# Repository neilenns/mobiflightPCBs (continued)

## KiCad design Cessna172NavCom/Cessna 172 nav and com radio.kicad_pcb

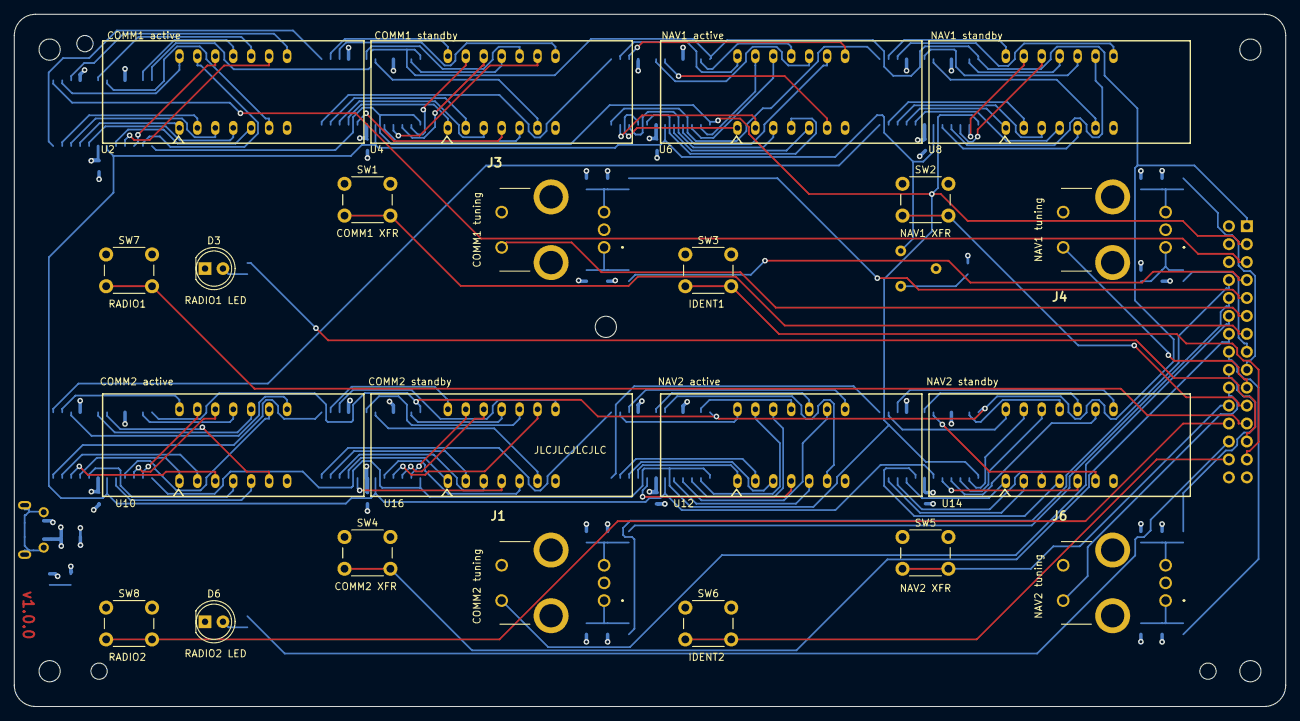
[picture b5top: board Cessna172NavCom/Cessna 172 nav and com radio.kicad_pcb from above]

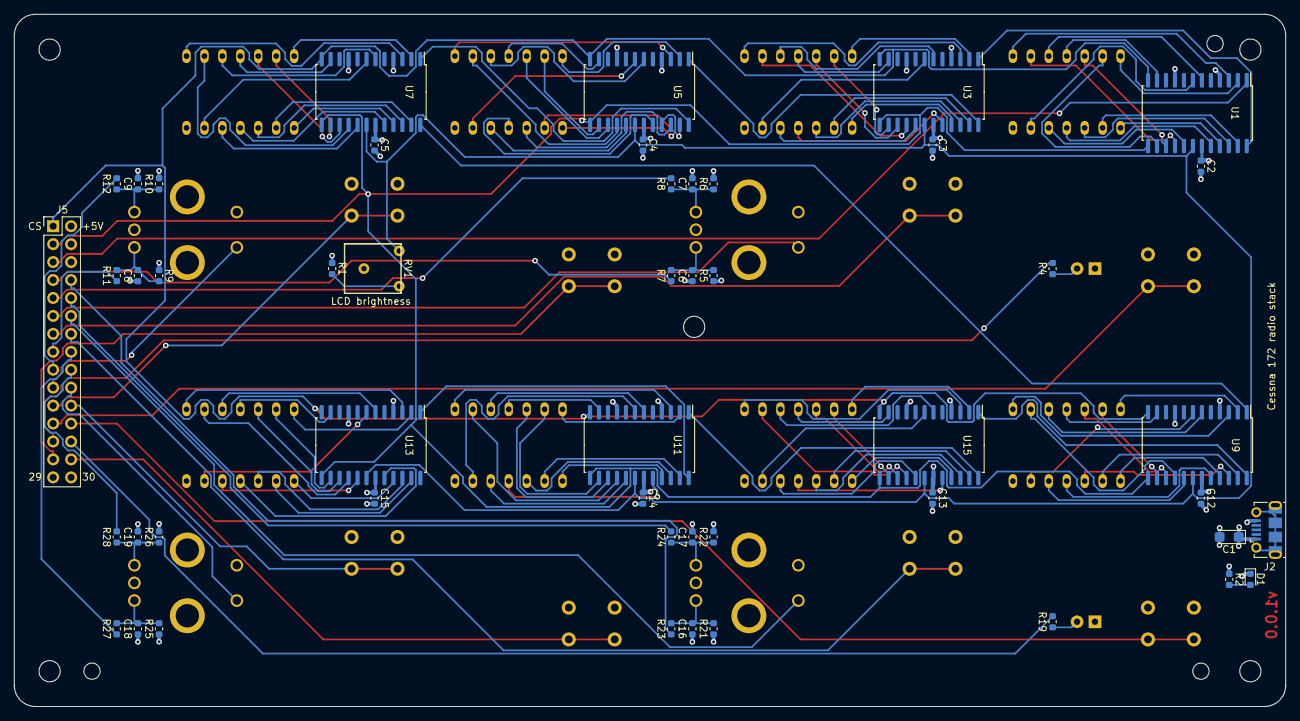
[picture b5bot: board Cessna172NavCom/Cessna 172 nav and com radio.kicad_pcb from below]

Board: 4 copper layers, 180.0 x 98.0 mm, 76 parts (49 on the bottom side), 151 nets.

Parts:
C1: 10uF; CP_EIA-3216-18_Kemet-A
C2, C3, C4, C5, C12, C13, C14, C15: 0.1uF; C_0603_1608Metric
C6, C7, C8, C9, C16, C17, C18, C19: 0.01uf; C_0603_1608Metric
D1: LED; LED_0603_1608Metric
D3, D6: LED; LED_D5.0mm
H1, H2, H3, H4, H5: MountingHole_3mm
J1, J3, J4, J6: EN11-HSM1BF20; EN11HSM1BF20
J2: USB_B_Micro; USB_Micro-B_Molex-105017-0001
J5: Conn_02x15_Odd_Even; PinHeader_2x15_P2.54mm_Vertical
R1, R2, R4, R19: 220k; R_0603_1608Metric
R5, R6, R7, R8, R9, R10, R11, R12, R21, R22, R23, R24, R25, R26, R27, R28: 10k; R_0603_1608Metric
RV1: 100k; A-2506 trimpot resistor
SW1, SW2, SW3, SW4, SW5, SW6, SW7, SW8: SW_Push; SW_PUSH_6mm_H8mm
U1, U3, U5, U7, U9, U11, U13, U15: MAX7219 COM standby; SOIC-24W_7.5x15.4mm_P1.27mm
U2, U4, U6, U8, U10, U12, U14, U16: 3651A

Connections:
+5V: C1.1, C2.1, C3.1, C4.1, C5.1, C12.1, C13.1, C14.1, C15.1, J2.1, J5.2, R1.1, R2.1, R5.1, R6.2, R9.1, R10.2, R21.1, R22.2, R25.1, R26.2, U1.19, U3.19, U5.19, U7.19, U9.19, U11.19, U13.19, U15.19
/5 digit LCD display/DIG_0: U1.2, U2.14
/5 digit LCD display/DIG_1: U1.11, U2.11
/5 digit LCD display/DIG_2: U1.6, U2.10
/5 digit LCD display/DIG_3: U1.7, U2.6
/5 digit LCD display/DIG_4: U1.3, U2.8
/5 digit LCD display/SEG_A: U1.14, U2.13
/5 digit LCD display/SEG_B: U1.16, U2.9
/5 digit LCD display/SEG_C: U1.20, U2.4
/5 digit LCD display/SEG_D: U1.23, U2.2
/5 digit LCD display/SEG_DP: U1.22, U2.3
/5 digit LCD display/SEG_E: U1.21, U2.1
/5 digit LCD display/SEG_F: U1.15, U2.12
/5 digit LCD display/SEG_G: U1.17, U2.5
/Tuning rotary encoder and switch/A1: C6.2, J3.A1, R5.2, R7.2
/Tuning rotary encoder and switch/B1: C7.1, J3.B1, R6.1, R8.1
/sheet5F5DD32A/A1: C8.2, J4.A1, R9.2, R11.2
/sheet5F5DD32A/B1: C9.1, J4.B1, R10.1, R12.1
/sheet5F68A9C2/DIG_0: U9.2, U10.14
/sheet5F68A9C2/DIG_1: U9.11, U10.11
/sheet5F68A9C2/DIG_2: U9.6, U10.10
/sheet5F68A9C2/DIG_3: U9.7, U10.6
/sheet5F68A9C2/DIG_4: U9.3, U10.8
/sheet5F68A9C2/DIN: U7.24, U9.1
/sheet5F68A9C2/SEG_A: U9.14, U10.13
/sheet5F68A9C2/SEG_B: U9.16, U10.9
/sheet5F68A9C2/SEG_C: U9.20, U10.4
/sheet5F68A9C2/SEG_D: U9.23, U10.2
/sheet5F68A9C2/SEG_DP: U9.22, U10.3
/sheet5F68A9C2/SEG_E: U9.21, U10.1
/sheet5F68A9C2/SEG_F: U9.15, U10.12
/sheet5F68A9C2/SEG_G: U9.17, U10.5
/sheet5F68A9C3/DIG_0: U11.2, U12.14
/sheet5F68A9C3/DIG_1: U11.11, U12.11
/sheet5F68A9C3/DIG_2: U11.6, U12.10
/sheet5F68A9C3/DIG_3: U11.7, U12.6
/sheet5F68A9C3/DIG_4: U11.3, U12.8
/sheet5F68A9C3/DIN: U11.1, U15.24
/sheet5F68A9C3/SEG_A: U11.14, U12.13
/sheet5F68A9C3/SEG_B: U11.16, U12.9
/sheet5F68A9C3/SEG_C: U11.20, U12.4
/sheet5F68A9C3/SEG_D: U11.23, U12.2
/sheet5F68A9C3/SEG_DP: U11.22, U12.3
/sheet5F68A9C3/SEG_E: U11.21, U12.1
/sheet5F68A9C3/SEG_F: U11.15, U12.12
/sheet5F68A9C3/SEG_G: U11.17, U12.5
/sheet5F68A9C4/DIG_0: U13.2, U14.14
/sheet5F68A9C4/DIG_1: U13.11, U14.11
/sheet5F68A9C4/DIG_2: U13.6, U14.10
/sheet5F68A9C4/DIG_3: U13.7, U14.6
/sheet5F68A9C4/DIG_4: U13.3, U14.8
/sheet5F68A9C4/DIN: U11.24, U13.1
/sheet5F68A9C4/SEG_A: U13.14, U14.13
/sheet5F68A9C4/SEG_B: U13.16, U14.9
/sheet5F68A9C4/SEG_C: U13.20, U14.4
/sheet5F68A9C4/SEG_D: U13.23, U14.2
/sheet5F68A9C4/SEG_DP: U13.22, U14.3
/sheet5F68A9C4/SEG_E: U13.21, U14.1
/sheet5F68A9C4/SEG_F: U13.15, U14.12
/sheet5F68A9C4/SEG_G: U13.17, U14.5
/sheet5F68A9C5/DIG_0: U15.2, U16.14
/sheet5F68A9C5/DIG_1: U15.11, U16.11
/sheet5F68A9C5/DIG_2: U15.6, U16.10
/sheet5F68A9C5/DIG_3: U15.7, U16.6
/sheet5F68A9C5/DIG_4: U15.3, U16.8
/sheet5F68A9C5/DIN: U9.24, U15.1
/sheet5F68A9C5/SEG_A: U15.14, U16.13
/sheet5F68A9C5/SEG_B: U15.16, U16.9
/sheet5F68A9C5/SEG_C: U15.20, U16.4
/sheet5F68A9C5/SEG_D: U15.23, U16.2
/sheet5F68A9C5/SEG_DP: U15.22, U16.3
/sheet5F68A9C5/SEG_E: U15.21, U16.1
/sheet5F68A9C5/SEG_F: U15.15, U16.12
/sheet5F68A9C5/SEG_G: U15.17, U16.5
/sheet5F71BCD2/A1: C16.2, J1.A1, R21.2, R23.2
/sheet5F71BCD2/B1: C17.1, J1.B1, R22.1, R24.1
/sheet5F71BCD3/A1: C18.2, J6.A1, R25.2, R27.2
/sheet5F71BCD3/B1: C19.1, J6.B1, R26.1, R28.1
/sheet5F611637/DIG_0: U3.2, U4.14
/sheet5F611637/DIG_1: U3.11, U4.11
/sheet5F611637/DIG_2: U3.6, U4.10
/sheet5F611637/DIG_3: U3.7, U4.6
/sheet5F611637/DIG_4: U3.3, U4.8
/sheet5F611637/DIN: U1.24, U3.1
/sheet5F611637/SEG_A: U3.14, U4.13
/sheet5F611637/SEG_B: U3.16, U4.9
/sheet5F611637/SEG_C: U3.20, U4.4
/sheet5F611637/SEG_D: U3.23, U4.2
/sheet5F611637/SEG_DP: U3.22, U4.3
/sheet5F611637/SEG_E: U3.21, U4.1
/sheet5F611637/SEG_F: U3.15, U4.12
/sheet5F611637/SEG_G: U3.17, U4.5
/sheet5F613960/DIG_0: U5.2, U6.14
/sheet5F613960/DIG_1: U5.11, U6.11
/sheet5F613960/DIG_2: U5.6, U6.10
/sheet5F613960/DIG_3: U5.7, U6.6
/sheet5F613960/DIG_4: U5.3, U6.8
/sheet5F613960/DIN: U3.24, U5.1
/sheet5F613960/SEG_A: U5.14, U6.13
/sheet5F613960/SEG_B: U5.16, U6.9
/sheet5F613960/SEG_C: U5.20, U6.4
/sheet5F613960/SEG_D: U5.23, U6.2
/sheet5F613960/SEG_DP: U5.22, U6.3
/sheet5F613960/SEG_E: U5.21, U6.1
/sheet5F613960/SEG_F: U5.15, U6.12
/sheet5F613960/SEG_G: U5.17, U6.5
/sheet5F613961/DIG_0: U7.2, U8.14
/sheet5F613961/DIG_1: U7.11, U8.11
/sheet5F613961/DIG_2: U7.6, U8.10
/sheet5F613961/DIG_3: U7.7, U8.6
/sheet5F613961/DIG_4: U7.3, U8.8
/sheet5F613961/DIN: U5.24, U7.1
/sheet5F613961/SEG_A: U7.14, U8.13
/sheet5F613961/SEG_B: U7.16, U8.9
/sheet5F613961/SEG_C: U7.20, U8.4
/sheet5F613961/SEG_D: U7.23, U8.2
/sheet5F613961/SEG_DP: U7.22, U8.3
/sheet5F613961/SEG_E: U7.21, U8.1
/sheet5F613961/SEG_F: U7.15, U8.12
/sheet5F613961/SEG_G: U7.17, U8.5
CLK: J5.3, U1.13, U3.13, U5.13, U7.13, U9.13, U11.13, U13.13, U15.13
COMM1_KHZ_SW: J3.D1, J5.11
COMM1_LEFT: J5.7, R7.1
COMM1_RIGHT: J5.9, R8.2
COMM1_XFR: J5.13, SW1.2
COMM2_KHZ_SW: J1.D1, J5.12
COMM2_LEFT: J5.8, R23.1
COMM2_RIGHT: J5.10, R24.2
COMM2_XFR: J5.14, SW4.2
CS_LOAD: J5.1, U1.12, U3.12, U5.12, U7.12, U9.12, U11.12, U13.12, U15.12
DIN: J5.5, U1.1
GND: C1.2, C2.2, C3.2, C4.2, C5.2, C6.1, C7.2, C8.1, C9.2, C12.2, C13.2, C14.2, C15.2, C16.1, C17.2, C18.1, C19.2, D1.1, D3.1, D6.1, J1.C1, J1.E1, J2.5, J3.C1, J3.E1, J4.C1, J4.E1, J5.4, J5.29, J5.30, J6.C1, J6.E1, SW1.1, SW2.1, SW3.1, SW4.1, SW5.1, SW6.1, SW7.1, SW8.1, U1.4, U1.9, U3.4, U3.9, U5.4, U5.9, U7.4, U7.9, U9.4, U9.9, U11.4, U11.9, U13.4, U13.9, U15.4, U15.9
IDENT1_SW: J5.27, SW3.2
IDENT2_SW: J5.28, SW6.2
ISET: RV1.3, U1.18, U3.18, U5.18, U7.18, U9.18, U11.18, U13.18, U15.18
NAV1_KHZ_SW: J4.D1, J5.19
NAV1_LEFT: J5.15, R11.1
NAV1_RIGHT: J5.17, R12.2
NAV1_XFR: J5.21, SW2.2
NAV2_KHZ_SW: J5.20, J6.D1
NAV2_LEFT: J5.16, R27.1
NAV2_RIGHT: J5.18, R28.2
NAV2_XFR: J5.22, SW5.2
unnamed: D1.2, R2.2
unnamed: D3.2, R4.1
unnamed: D6.2, R19.1
unnamed: R1.2, RV1.1
RADIO1_LED: J5.25, R4.2
RADIO1_SW: J5.23, SW7.2
RADIO2_LED: J5.26, R19.2
RADIO2_SW: J5.24, SW8.2

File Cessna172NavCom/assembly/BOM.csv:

Comment,Designator,Footprint,LCSC
"10uF","C1","Capacitor_THT:CP_Radial_D5.0mm_P2.00mm",""
"0.1uF","C2,C3,C4,C5,C12,C13,C14,C15","Capacitor_SMD:C_0805_2012Metric_Pad1.15x1.40mm_HandSolder"," C49678"
"0.01uf","C6,C7,C8,C9,C16,C17,C18,C19","Capacitor_SMD:C_0805_2012Metric_Pad1.15x1.40mm_HandSolder"," C1710"
"LED","D1","LED_SMD:LED_0805_2012Metric_Pad1.15x1.40mm_HandSolder","C2293"
"LED","D3,D6","LED_THT:LED_D5.0mm",""
"USB_B_Micro","J2","Connector_USB:USB_Micro-B_Molex-105017-0001",""
"EN11-HSM1BF20","J1,J3,J4,J6","SamacSys_Parts:EN11HSM1BF20",""
"Conn_02x15_Odd_Even","J5","Connector_PinHeader_2.54mm:PinHeader_2x15_P2.54mm_Vertical",""
"220","R1,R2,R4,R19","Resistor_SMD:R_0805_2012Metric_Pad1.15x1.40mm_HandSolder","C17540"
"10k","R5,R6,R7,R8,R9,R10,R11,R12,R21,R22,R23,R24,R25,R26,R27,R28","Resistor_SMD:R_0805_2012Metric_Pad1.15x1.40mm_HandSolder","C17414"
"100k","RV1","Cessna 172 nav and com radio:A-2506 trimpot resistor",""
"SW_Push","SW1,SW2,SW3,SW4,SW5,SW6,SW7,SW8","Button_Switch_THT:SW_PUSH_6mm_H8mm",""
"MAX7219 COM standby","U1,U3,U5,U7,U9,U11,U13,U15","Package_SO:SOIC-24W_7.5x15.4mm_P1.27mm","C9964"
"3651A","U2,U4,U6,U8,U10,U12,U14,U16","Cessna 172 nav and com radio:3651A",""

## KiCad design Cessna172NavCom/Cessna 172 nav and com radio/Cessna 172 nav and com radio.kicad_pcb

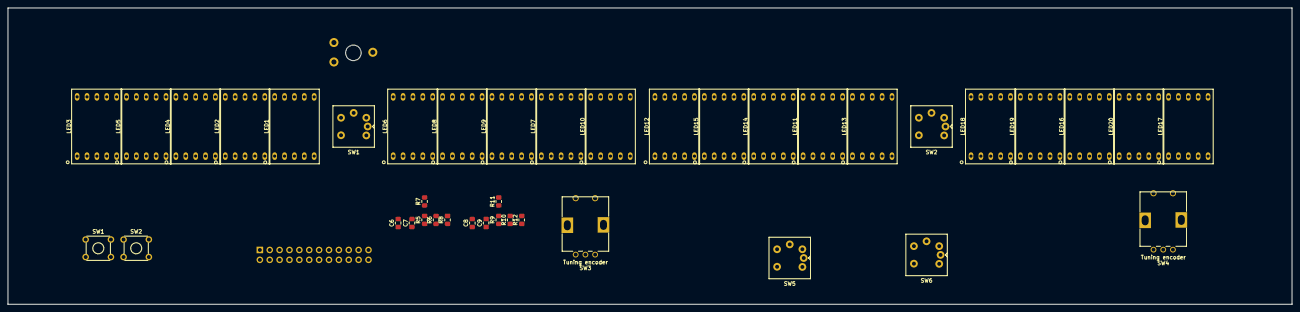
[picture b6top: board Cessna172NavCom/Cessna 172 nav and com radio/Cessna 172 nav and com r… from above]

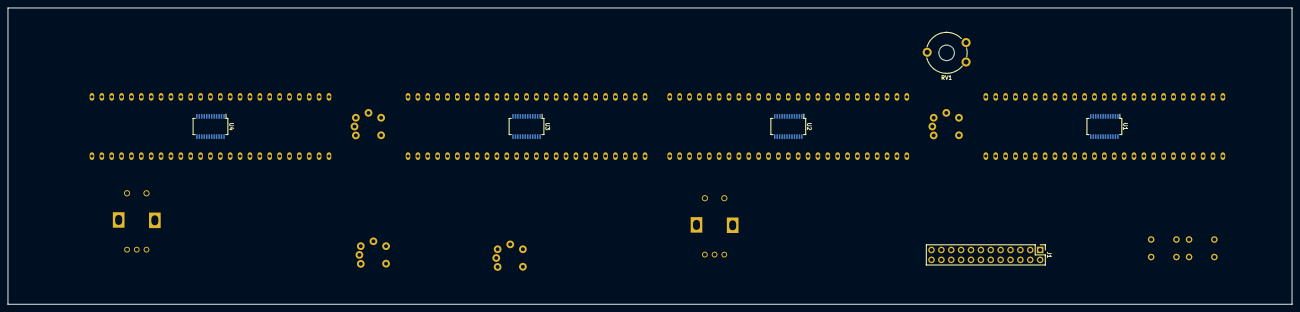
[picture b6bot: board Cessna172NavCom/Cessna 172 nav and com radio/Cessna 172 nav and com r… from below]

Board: 2 copper layers, 330.2 x 76.2 mm, 46 parts (6 on the bottom side), 77 nets, no tracks yet.

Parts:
C6, C7, C8, C9: 0.1uf; C_0805_2012Metric_Pad1.15x1.40mm_HandSolder
J1: Conn_02x12_Odd_Even; PinHeader_2x12_P2.54mm_Vertical
LED1, LED6, LED11, LED16: MobiFlight digit 5; KYX-5101AS
LED2, LED7, LED12, LED17: MobiFlight digit 4; KYX-5101AS
LED3, LED8, LED13, LED18: MobiFlight digit 2; KYX-5101AS
LED4, LED9, LED14, LED19: MobiFlight digit 1; KYX-5101AS
LED5, LED10, LED15, LED20: Mobiflight digit 0; KYX-5101AS
R5, R6, R7, R8, R9, R10, R11, R12: 10k; R_0805_2012Metric_Pad1.15x1.40mm_HandSolder
RV1: 100k; Potentiometer_Piher_PT-10-V10_Vertical_Hole
SW1: COMM transfer switch; SW_TH_Tactile_Omron_B3F-10xx
SW1#2: COMM toggle; B3W-9000-xxx
SW2: NAV transfer switch; SW_TH_Tactile_Omron_B3F-10xx
SW2#2: NAV toggle; B3W-9000-xxx
SW3, SW4: Tuning encoder; EN11-HSM1BF20
SW5: Test switch; B3W-9000-xxx
SW6: Ident switch; B3W-9000-xxx
U1, U2, U3, U4: MAX7219 COM standby; SSOP-24_3.9x8.7mm_P0.635mm

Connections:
+5V: J1.1, R5.2, R6.2, R9.2, R10.2, U1.19, U2.19, U3.19, U4.19
/5 digit LCD display/DIG_0: LED5.8, U1.2
/5 digit LCD display/DIG_1: LED4.8, U1.11
/5 digit LCD display/DIG_2: LED3.8, U1.6
/5 digit LCD display/DIG_3: LED2.8, U1.7
/5 digit LCD display/DIG_4: LED1.8, U1.3
/5 digit LCD display/SEG_A: LED1.7, LED2.7, LED3.7, LED4.7, LED5.7, U1.14
/5 digit LCD display/SEG_B: LED1.6, LED2.6, LED3.6, LED4.6, LED5.6, U1.16
/5 digit LCD display/SEG_C: LED1.4, LED2.4, LED3.4, LED4.4, LED5.4, U1.20
/5 digit LCD display/SEG_D: LED1.2, LED2.2, LED3.2, LED4.2, LED5.2, U1.23
/5 digit LCD display/SEG_DP: LED1.5, LED2.5, LED3.5, LED4.5, LED5.5, U1.22
/5 digit LCD display/SEG_E: LED1.1, LED2.1, LED3.1, LED4.1, LED5.1, U1.21
/5 digit LCD display/SEG_F: LED1.9, LED2.9, LED3.9, LED4.9, LED5.9, U1.15
/5 digit LCD display/SEG_G: LED1.10, LED2.10, LED3.10, LED4.10, LED5.10, U1.17
/sheet5F611637/DIG_0: LED10.8, U2.2
/sheet5F611637/DIG_1: LED9.8, U2.11
/sheet5F611637/DIG_2: LED8.8, U2.6
/sheet5F611637/DIG_3: LED7.8, U2.7
/sheet5F611637/DIG_4: LED6.8, U2.3
/sheet5F611637/DIN: U1.24, U2.1
/sheet5F611637/SEG_A: LED6.7, LED7.7, LED8.7, LED9.7, LED10.7, U2.14
/sheet5F611637/SEG_B: LED6.6, LED7.6, LED8.6, LED9.6, LED10.6, U2.16
/sheet5F611637/SEG_C: LED6.4, LED7.4, LED8.4, LED9.4, LED10.4, U2.20
/sheet5F611637/SEG_D: LED6.2, LED7.2, LED8.2, LED9.2, LED10.2, U2.23
/sheet5F611637/SEG_DP: LED6.5, LED7.5, LED8.5, LED9.5, LED10.5, U2.22
/sheet5F611637/SEG_E: LED6.1, LED7.1, LED8.1, LED9.1, LED10.1, U2.21
/sheet5F611637/SEG_F: LED6.9, LED7.9, LED8.9, LED9.9, LED10.9, U2.15
/sheet5F611637/SEG_G: LED6.10, LED7.10, LED8.10, LED9.10, LED10.10, U2.17
/sheet5F613960/DIG_0: LED15.8, U3.2
/sheet5F613960/DIG_1: LED14.8, U3.11
/sheet5F613960/DIG_2: LED13.8, U3.6
/sheet5F613960/DIG_3: LED12.8, U3.7
/sheet5F613960/DIG_4: LED11.8, U3.3
/sheet5F613960/DIN: U2.24, U3.1
/sheet5F613960/SEG_A: LED11.7, LED12.7, LED13.7, LED14.7, LED15.7, U3.14
/sheet5F613960/SEG_B: LED11.6, LED12.6, LED13.6, LED14.6, LED15.6, U3.16
/sheet5F613960/SEG_C: LED11.4, LED12.4, LED13.4, LED14.4, LED15.4, U3.20
/sheet5F613960/SEG_D: LED11.2, LED12.2, LED13.2, LED14.2, LED15.2, U3.23
/sheet5F613960/SEG_DP: LED11.5, LED12.5, LED13.5, LED14.5, LED15.5, U3.22
/sheet5F613960/SEG_E: LED11.1, LED12.1, LED13.1, LED14.1, LED15.1, U3.21
/sheet5F613960/SEG_F: LED11.9, LED12.9, LED13.9, LED14.9, LED15.9, U3.15
/sheet5F613960/SEG_G: LED11.10, LED12.10, LED13.10, LED14.10, LED15.10, U3.17
/sheet5F613961/DIG_0: LED20.8, U4.2
/sheet5F613961/DIG_1: LED19.8, U4.11
/sheet5F613961/DIG_2: LED18.8, U4.6
/sheet5F613961/DIG_3: LED17.8, U4.7
/sheet5F613961/DIG_4: LED16.8, U4.3
/sheet5F613961/DIN: U3.24, U4.1
/sheet5F613961/SEG_A: LED16.7, LED17.7, LED18.7, LED19.7, LED20.7, U4.14
/sheet5F613961/SEG_B: LED16.6, LED17.6, LED18.6, LED19.6, LED20.6, U4.16
/sheet5F613961/SEG_C: LED16.4, LED17.4, LED18.4, LED19.4, LED20.4, U4.20
/sheet5F613961/SEG_D: LED16.2, LED17.2, LED18.2, LED19.2, LED20.2, U4.23
/sheet5F613961/SEG_DP: LED16.5, LED17.5, LED18.5, LED19.5, LED20.5, U4.22
/sheet5F613961/SEG_E: LED16.1, LED17.1, LED18.1, LED19.1, LED20.1, U4.21
/sheet5F613961/SEG_F: LED16.9, LED17.9, LED18.9, LED19.9, LED20.9, U4.15
/sheet5F613961/SEG_G: LED16.10, LED17.10, LED18.10, LED19.10, LED20.10, U4.17
CLK: J1.4, U1.13, U2.13, U3.13, U4.13
COMM_LEFT: J1.8, R8.2
COMM_RIGHT: J1.10, R7.1
COMM_TX_LED: J1.16, SW1.4, SW1#2.6
COMM_TX_SW: J1.14, SW1.2, SW1#2.4
DIN: J1.6, U1.1
GND: C6.1, C7.2, C8.1, C9.2, J1.3, SW1.1, SW1.3, SW1#2.3, SW1#2.5, SW2.1, SW2.3, SW2#2.3, SW2#2.5, SW5.3, SW5.5, SW6.3, SW6.5, U1.4, U1.9, U2.4, U2.9, U3.4, U3.9, U4.4, U4.9
IDENT_LED: J1.23, SW6.6
IDENT_SW: J1.21, SW6.4
ISET: RV1.3, U1.18, U2.18, U3.18, U4.18
LOAD: J1.2, U1.12, U2.12, U3.12, U4.12
NAV_LEFT: J1.5, R12.2
NAV_RIGHT: J1.7, R11.1
NAV_TX_LED: J1.13, SW2.4, SW2#2.6
NAV_TX_SW: J1.11, SW2.2, SW2#2.4
unnamed: C6.2, R5.1, R7.2
unnamed: C7.1, R6.1, R8.1
unnamed: C8.2, R9.1, R11.2
unnamed: C9.1, R10.1, R12.1
TEST_LED: J1.20, SW5.6
TEST_SW: J1.18, SW5.4

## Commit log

2020-09-12 Initial schema
2020-09-12 Minor update
2020-09-12 Five digit displays wired up
2020-09-12 Add rotary encoder
2020-09-12 3D model for LED
2020-09-12 3d model updates
2020-09-12 Updated schematic to include remaining items.
2020-09-12 Proper LED buttons and switches
2020-09-12 More 3D models, footprints, and manuals
2020-09-12 Switch footprint
2020-09-12 Tactile switch
2020-09-13 Fix up paths
2020-09-13 Traces for one LCD bank complete
2020-09-13 LEDs and power jack
2020-09-13 First full layout attempt, new 3D models
2020-09-13 Re-work to use 5 digit LEDs
2020-09-15 New board size!
2020-09-17 Switch to USB for power, all parts on board
2020-09-17 Updated board size and parts placement
2020-09-17 Updated rotary encoder with proper footprint
2020-09-17 Connection, footprint, and layout updates
2020-09-18 Auto-router files
2020-09-18 Updated trace width for +5V and GND
2020-09-18 Mostly laid out
2020-09-18 Full 2up layout done
2020-09-19 Position changes for routing
2020-09-19 Move things around to try and help router
2020-09-19 Fix courtyard overlap for routing
2020-09-19 New encoder design
2020-09-19 Fully routed woot woot!
2020-09-19 Fully routed!!!
2020-09-19 Minor PCB cleanup
2020-09-22 Add mobiflight files, start Arduino shield
2020-09-22 Remaining encoders and some buttons confirmed
2020-09-23 All comm and nav radio freq set and swap tested
2020-09-23 Remove unnecessary items, rename some of the nets
2020-09-23 Switch to 30 pin connector for availability reasons
2020-09-23 Schematic renumbering
2020-09-24 Arduino shield plus more main board changes
2020-09-24 Added autoroute and pour
2020-09-24 Re-routed with new LED position
2020-09-26 Finally done maybe for real
2020-09-26 Smaller components and output for JLC
2020-09-26 Ready for 0805 production
2020-09-27 Final version submitted for assembly
2020-10-08 Configs that work with the v1 board
2020-10-08 A bunch of the knobs are working now
2020-10-09 Working on a new board
2020-10-09 New board ready
2020-10-10 Updated secondary display
2020-10-11 more autopilot changes
2020-10-12 Submitted version!
2020-11-05 Mobiflight config for actual build
2021-07-20 Updated mobiflight configurations to use SimConnect events
2021-07-29 Add new board for TBM930
2021-07-30 TBM930 updates
2021-08-14 Switch to use the LED driver chip
2021-08-15 Create global library for footprints and symbols
2021-08-16 Massive de-ice panel update
2021-08-16 Routed!
2021-08-16 Before switching to Pro Micro
2021-08-16 Switch to smaller Arduino
2021-08-16 More PCB markings
2021-08-17 Minor changes
2021-08-18 Microcontroller righton the board
2021-08-18 Placed components on PCB, working on routing
2021-08-19 More atmega32u4 routing
2021-08-19 Everything is routed!
2021-08-19 Schematic submitted to microtype
2021-08-19 Schematic updates based on MT engineering discord feedback
2021-08-20 Additional reset components
2021-08-20 Fix 12V routing
2021-08-21 Massive PCB reroute
2021-08-21 Fully routed v2
2021-08-23 Switch to TQFP
2021-08-23 Lots of minor updates to silk screen and vias
2021-08-24 USB breakout board
2021-08-24 Add labels, change header
2021-08-25 Adjust the spacing of PCB components, reroute data trace
2021-08-25 Swap to different USB footprint
2021-08-25 More footprint changes
2021-08-25 Upsize all the connectors
2021-08-26 Final gerbers for USB breakout board
2021-08-26 Change connector, fix BOM
2021-09-04 Breakout board and tbm930 board updates
2021-09-05 Remove old files
2021-09-06 Update to support the new board!
2021-09-07 Cleanup references so it should open on any machine
2021-09-07 Move MobiFlight config into de-ice panel folder
2021-09-07 Add missing BOM and TBM930 mods
2021-09-07 Add missing BOM files
2021-09-09 Fix errors in the panel configs
2021-09-11 Initial version
2021-09-11 Add all the inputs
2021-09-15 More AP updates
2021-09-15 Add bom for de-ice panel
2021-09-15 Move ibom to gh pages
2021-09-16 Add schematic PDF
2021-09-16 Testing kibot in github actions
2021-09-16 Try single quotes
2021-09-16 Add manual trigger
2021-09-16 Remove manual trigger
2021-09-16 Try without spaces in folder name
2021-09-16 Remove spaces from filenames
2021-09-16 Change case
2021-09-16 Update outputs generated
2021-09-16 Remove logo file
2021-09-16 Remove more logos
2021-09-16 Add JLCPCB pos and BOM files
2021-09-16 Add JLCPCB BOM and pos files
2021-09-16 Fix YAML errors
2021-09-16 Try fixing rotation
2021-09-16 Try fixing exclude filter
2021-09-16 Fix JLCPCB generation
2021-09-16 Add VSCode dev container for KiBot
2021-09-16 Move all fab files to dedicated folder
2021-09-16 Working ibom generation, JLCPCB generation
2021-09-16 Fix PCB holes
2021-09-16 Fix silkscreen position
2021-09-16 Everything working!
2021-09-16 Add version numbers and license
2021-09-16 Enable ERC/DRC/fills
2021-09-16 Refactor yaml and fix github action
2021-09-16 Change footprint for terminal block
2021-09-16 Commit to trigger workflow
2021-09-16 Fix github action
2021-09-16 Try fixing STEP errors
2021-09-16 Remove STEP because it was causing so much trouble
2021-09-16 Try fixing output folders
2021-09-16 Add board/schematic back in
2021-10-28 Initial CJ4 configuration, plus G1000/G3000 fixes
2021-10-29 Fix switches for avionics, add input shifters
2021-10-31 More WT CJ4 changes
2021-12-12 Add cub crafter config
2022-01-15 MF config file changes
2022-04-05 G1000 nxi updates, CJ4 WT4 updates
2022-12-06 Updated config files
2022-12-06 Add FMS co-pilot, fix remaining issues
2022-12-07 More updates for the CJ4 AAU1
2022-12-07 Update to hide the yoke automatically
2022-12-08 More CJ4 AAU1 updates
2023-01-21 Tons of mapping updates
2023-01-21 More panel updates
2023-02-06 Updated CJ4 AAU1 stuff
2023-02-11 Lots of updates
2023-02-20 Config updates
2024-05-03 Updated configs
2024-11-22 CJ4 2024 changes
2024-11-22 C172 for MSFS2024
2024-11-23 All bvars updated for CJ4
